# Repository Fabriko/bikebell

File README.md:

# 

Improving cycle networks by rich, passionately gathered user-generated data:

* allows riders to share and easily feed back on experiences
* provides planners and maintainers with authentic, current, precise, and meaningful information for their decisions

4 components in early development:

* [Hardware casing](Hardware/case),
* _Firmware_,
* [Cross-platform smartphone app](MobileApp),
* [Web-based analysis suite](DataAnalysis).

_Data is open, but anonymised by default._

**Data gets more valuable to planners as it builds.**

The _product_ is better cycling options, with the end result of further conversions.

We completed a funded pilot in late 2015. In 2016, we further developed it in partnership for a phased Auckland study relating to transport modal shifting.

We develop this for love where we can and [pitch for further funding](./pitch.md) so we can continue. We'd love to get payed to advance something that benefits nearly everyone.

A little more information is available on the [Sensibel website](http://sensibel.org).

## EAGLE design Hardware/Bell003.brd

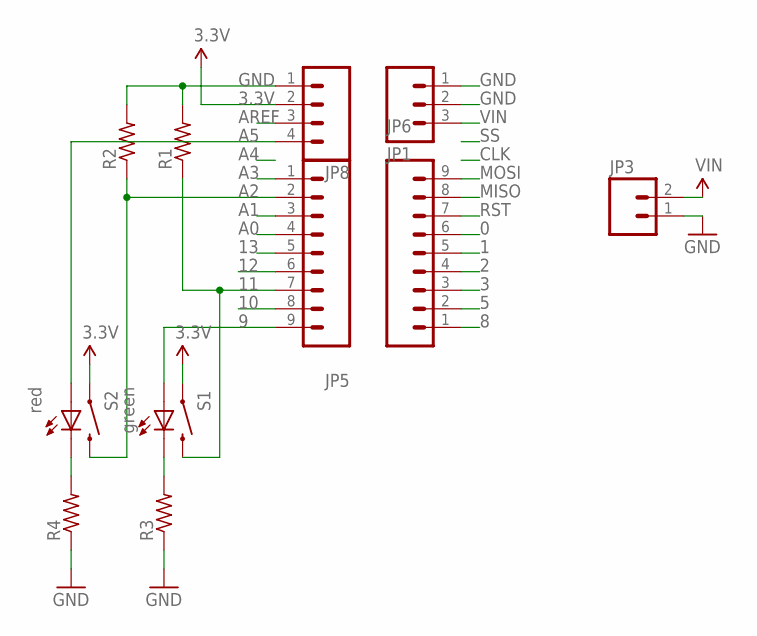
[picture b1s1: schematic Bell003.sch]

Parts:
JP1: M03PTH; 1X03
JP3: M02-JST-2-PTH-NO_SILK; JST-2-PTH-NS
JP5, JP6: M09; 1X09
JP8: M04PTH; 1X04
R1, R2, R3, R4: RES-US1206FAB; R1206FAB
S1: green; TACTILE-PTH-LED-12MM
S2: red; TACTILE-PTH-LED-12MM

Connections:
0: JP6.6
1: JP6.5
2: JP6.4
3: JP6.3
3.3V: JP8.2, S1.4 (1), S2.4 (1)
5: JP6.2
8: JP6.1
9: JP5.9, S1.A
10: JP5.8
11: JP5.7, R1.1, S1.2
12: JP5.6
13: JP5.5
A0: JP5.4
A1: JP5.3
A2: JP5.2, R2.1, S2.2
A3: JP5.1
A5: JP8.4, S2.A
AREF: JP8.3
GND: JP1.1, JP1.2, JP3.1, JP8.1, R1.2, R2.2, R3.1, R4.1
MISO: JP6.8
MOSI: JP6.9
unnamed: R3.2, S1.C
unnamed: R4.2, S2.C
RST: JP6.7
VIN: JP1.3, JP3.2

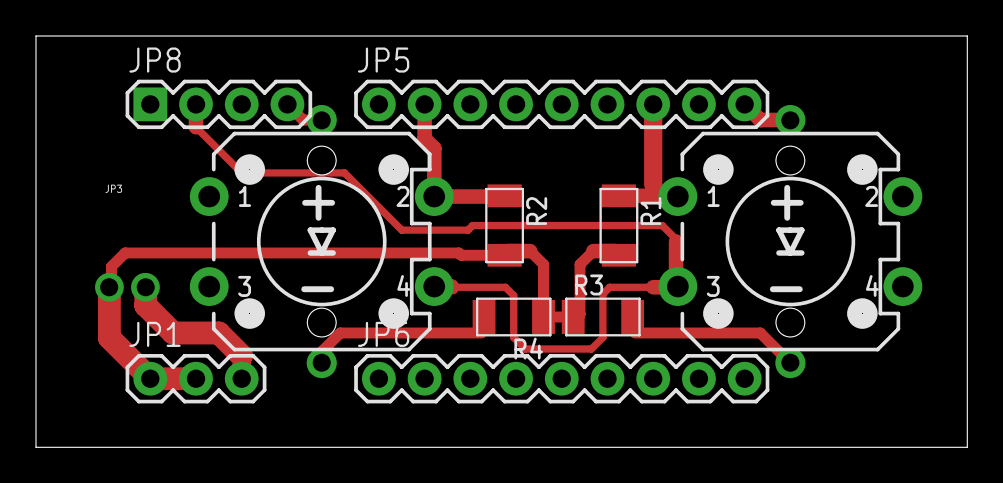
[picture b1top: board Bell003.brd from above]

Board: 2 copper layers, 51.7 x 22.9 mm, 11 parts (0 on the bottom side), 9 nets.

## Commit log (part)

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2015-08-17 Most functionality mostly working on at least one handset platform through evothings runtime only - kapish?
2015-08-19 Fix burger menu for Huawei trial device, GPS tested too
2015-08-27 Slight hack to get a better but still imperfect map position
2015-09-01 Add rudimentary config option to toggle the sensor being used to minimise chance of device-specific code overlap
2015-09-01 Small tweaks, wanted and started to abstract the sensor device and to include phone as a possibility
2015-09-02 Comment out link in index.html to sensor.js, which has not been committed yet
2015-09-02 Add important URL for evothings.ble docs
2015-09-03 Replace console buttons for intended simpler UX and workflow
2015-09-04 Switch to blend and suddenly we have dom problems with GPX
2015-09-04 Change GPX to a funky JSON custom timestamped format I call JSONtrail, hook it up and it kinda works
2015-09-04 Add button press data to trail and we are ready to go in the roughest way possible
2015-09-05 Rework pairings hack and logging around it - this is also the only way we can determine the handset ID / sensor name
2015-09-07 Slightly fixed up version of what we trialed with on 20150906. So several random panic changes and some pukka ones. Add jquery for some ajax to Amazon S3 (though problems\!). DIsable menu items for L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
2015-09-15 Change connection workflow and UI feedback: reconnect to known devices on disconnection; connect() uses entire deviceInfo object now not just device address; hardcode connection state codes (not clea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
2015-09-15 Style console timestamps and version output for readability, switch logActivity to use jQuery, add version into JSONtrail and makeGeoJSON
2015-09-15 Minor tweaks to console metadata styles and classes, more elegant and flexible, and version increment I forgot before
2015-09-15 Make UI buttons react to context
2015-09-15 Add rough menu nav inside header element
2015-09-16 Finish manual part of merge for pull request #1
2015-09-16 Remove some old files in root directory from before pull reuest #1
2015-09-16 Add enableButtonsWithoutGPS config setting and support it, mainly for testing bluetooth connectivity (enabling buttons) without GPS, add dummy data to config file
2015-11-18 UI using JQM, buggy burger menu, tabs widget, slight cleanup
2015-11-29 Clean up some cruft from old UI code in index.html
2015-11-30 Add basic connect, read, disconnect, and an attempt at LED for green light, disable non-implemented developer buttons
2015-12-02 Big adaptive button connects and, most importantly, morphs
2015-12-02 Big adaptive button connects and listens, add and implement disconnect button and method, add callbacks to methods and use them
2015-12-06 Faux connection tweaks and fixes: * Move faux connection predicate and handling from blend.conn() to blend.connectFromScratch(). * Make Fake connection a dev option toggle rather than an annoying dia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
2015-12-07 Journey support for new big adaptive button and faux connection: * Allow customisation of status message and next adaptive button on disconnect. * Add a maximum lag config option for POIs/waypoints. 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
2015-12-08 Some safe cleanup of comments and outdentation; remove global geoOptions, not needed because config.geoOptions
2015-12-08 Remove legacy journey buttons now we have adpativeButton
2015-12-10 Remove legacy cruft, split some functionality into new files ui.js, diagnostics.js, util.js, and (FWIW) _legacy.js (not sourced)
2015-12-10 Forgot to add .gitignore in previous commit
2015-12-12 Get a temporary read-only zoomed out map on Dashboard background. + wll use when waiting for GPS fix, then move to "live" background * add map creation options to drawMap() so I can make new one read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
2015-12-13 Add start property to rendering to allow default starting properties for a rendering, support it in drawMap()
2015-12-13 Set underlay images for Dashboard panel map as config.rendering.underlay
2015-12-13 Document stanza under DOMContentLoaded listener where I tried to get the intiial map size sorted with various techniques
2015-12-13 Clean off some obsolete comments in geo.js
2016-02-03 Move tab activate listener to document.pageinit in ui.js; move geolocation object fail block to where it should have been; add toast TODOs; indent TESTWatchId block; add mapbox.js stubs; finally get 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
2016-02-04 Fix map marker updating and following
2016-02-04 Add toast/notification on GPS result; assign location to L.LatLng; add polylines; movemarker creation to outer location call; add stub for journey GeoJSON fix; update dash marker PNG; ename TESTWatch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
2016-02-05 Add points from watchPosition if journey in progress; there is no medium duration for toast :/ ; tweak addData log message; version -> 0.3.1; add short notification (toast) feedback on button presses
2016-02-09 Fix relative link in top-level README to MobileApp README
2016-02-10 Start of track visualisation, loads from local GeoJSON file selector; based on previous project to load GPX files locally and contains some legacy from that
2016-06-04 Adds tiny tweaks to main README - grammar and usability
2016-06-04 Adds .gitignore at root dir to reduce git status output clutter
2016-06-04 Renames sensor device class to Sensor from App, moves legacy global instantiaytions from class library file, removes global ble object which seems unneeded
2016-06-06 Adds sensor connection/disconnection methods to Sensor, integrates into calling files, tweaks .gitignore
2016-06-08 Generates more descriptive title for tracks and allows user to rename them
2016-06-27 sensibel v2 printable case
2016-08-08 Adds full settings popup including required setting for rider name; adds rider name to track metadata
2016-08-08 Fixes a bug in error handling for geowatching; adds a .modal stanza to CSS, not really used though
2016-08-13 Half implemented new generation journey class with database backup, not integrated with buttons yet or tested after start journey stage
2016-08-16 Renames J2/T2 classes and j2 instance to sensib(le) Journey/Track and "journey"
2016-08-17 Adds popup markers with proof-of-concept edit forms for waypoints, involves returning waypoint, rejigs and renames markPosition() to markWaypoint()
2016-08-17 Sets up categories database table pretty crudely and hardcodedly for now
2016-08-19 Adds very rough hardcoded categories selection for waypoint notes
2016-09-24 moves Faux Connection Mode from config file to localStorage and puts a rough flipswitch in app settings popup; adds example journey map tile details; adds bucketName as localStorage setting which can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
2016-09-25 Adds coordinateProperties as per https://github.com/mapbox/geojson-coordinate-properties to geoJSON track
2016-09-26 Adds locally versioned (0.2.13) and too-difficult-recreate-but-available-on-request Journey Browser / data dashboard, shares config file with smartphone app for now; supports loading tracks, changing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
2016-09-30 Updates Leaflet to 1.0.0 because I'm an edgelord
2016-10-06 Small reformat and cleanup
2016-10-09 Adds configurable option (because it's a little flaky on poor GPS tracks) to show snapped trackpoints with tooltips showing times where available
2016-10-09 Corrects a DOM error that's been there the whole time!
2016-10-09 Adds genuine track metrics for length and buttons; sets button measure values as variables/constants finally; privatises some journeyRecord methods and renames private getPopupContent to _getPopupCon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
2016-10-11 Adds track duration stat to Journey Browser; unable to format as I'd hoped easily with jQuery, changes 'length' track property to 'distance'; reorders track property list; supporting CSS and utils ch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
2017-02-22 Autoconnects to BLE device if available
2017-02-26 Moves legacy DB code into storage.js for clearer diffing
2017-02-26 Sync of the real journey seems good, in parallel with local DB
2017-02-26 Adds slightly tested offline syncing; allows config option for database document prefixes, switches to UTC for document name core
2017-02-26 Adds PouchDB and syncs to remote, without replacing AWS code at this point
2017-02-27 Moves rendering spaghetti code to journeyRecord.render(); fixes turfjs exception on tracks which shouldn't happen which have to coordinates in their Linestrings
2017-02-27 Fixes good and bad points total and display
2017-02-27 Adds JourneyRecord.hideOn() which seems to work well enough!
2017-02-27 Restores functional status of track colour changer control
2017-02-27 Cleans up and reformats journey viewer code after refactor for new backend
2017-02-27 Adds live change watching and so far removes journeys using new JourneyRecord.remove()
2017-02-28 Adds basic streetview(tm) photo to track feature point popups on Journey Viewer
2017-02-28 Updates Leaflet to 1.0.3 in Journey Viewer
2017-02-28 CHecks streetview image metadata before loading but it's pretty slow, so gonna try pre-emptively loading and using DOM replacement after checking metadata on popup open; sort your crappy API out Goog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
2017-03-01 Adds streetview lightbox-style image popup, still needs close button; needed to upgrade to JQM 1.5alpha
2017-03-02 Fixes bug where streetview image can be added to popup every time it's opened
2017-03-03 Adds rudimentary reverse geocoding using nominatim.openstreetmap.org to map popups
2017-03-05 Adds necessarily ugly technique to fix order of response div elements in map popup
2017-03-06 Adds rudimentary UI as burger menu item and test of navigation.camera
2017-03-14 Wraps photo in file system request which simply creates directory for now
2017-03-15 Adds new class CapturedMedia in new file, basically farms out isolated code
2017-03-17 Adds some placeholder user settings for media upload and storage
2017-03-19 Adds media capture reference entry tpo existing journey tracks
2017-03-19 Adds loose GeoJSON Point files with correct filenames; adds CapturedMedia.uuid property
2017-04-24 Unstable WIP - frustration making a well-encoded AJAX post to Imgur API
2017-04-28 Adds working image upload (finally), needs cleaning and making asynchronous
2017-04-28 Places images in (potentially hidden) album on image host
2017-04-29 Adds captured media remote id and url metadata if not part of journey
2017-04-29 Adds remote media identifiers to both track and floating media point properties
2017-04-30 WIP to add function syncMedia to upload and complete metadata for unuploaded media files
2017-04-30 Trims string values in settings form before saving
2017-05-01 Changes categories remote source document to generic settings document and pushes categories list down a JSON level in that file
2017-05-01 Cleans up markWaypoint() from popup rejig
2017-05-08 Allows sync query that is not supported yet in PouchDB to be forced to execute remotely, where it works
2017-05-10 Adds media upload when online for media captured offline, and adding journey identifying data in journey file; capturedMedia now supports loading locally stored images
2017-05-11 Adds floating media uploads when online, doesn't sync DB afterwards yet; adds rider name to floating media metadata file (duh! - that's a fix)
2017-05-14 Fixes serious isseu where lat and lon are stored reversed for media coordinates (thanks for being special, GeoJSON)
2017-05-14 Adds media pins and popups with expandos in Journey Browser if part of journeys; floating media records not implemented
2017-05-15 Show media on app map
    * adds CaturedMedia.plot()
    * adds markMediapoint()
    * fixes lots of stuff that was broken or wrong

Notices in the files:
parts and their libraries:
SparkFun-Connectors: Licensing: Creative Commons ShareAlike 4.0 International - https://creativecommons.org/licenses/by-sa/4.0
